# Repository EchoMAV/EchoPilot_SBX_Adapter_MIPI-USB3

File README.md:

Created using KiCad 7.0.10

This is an open-source payload/camera adapter designed for the EchoPilot SBX series of boards. It is meant for a 2 or 4-lane MIPI camera (22 pin 0.5mm spacing, standard Nvidia and Rpi pinout) and an optional FLIR boson in conjunction with OEM Camera VPC3 board (https://www.oemcameras.com/rhp-bos-vpc3-if.htm?search=vpc). The board also includes a 100Mbps Ethernet port using a JST GH connector.

6 Layer PCB, 4/4 mil spacing, min hole size is 0.2mm
Note impedance controlled traces for MIPI, USB and Ethernet. Trace width and spacing may need to be adjusted depending on the stackup and materials used in production.

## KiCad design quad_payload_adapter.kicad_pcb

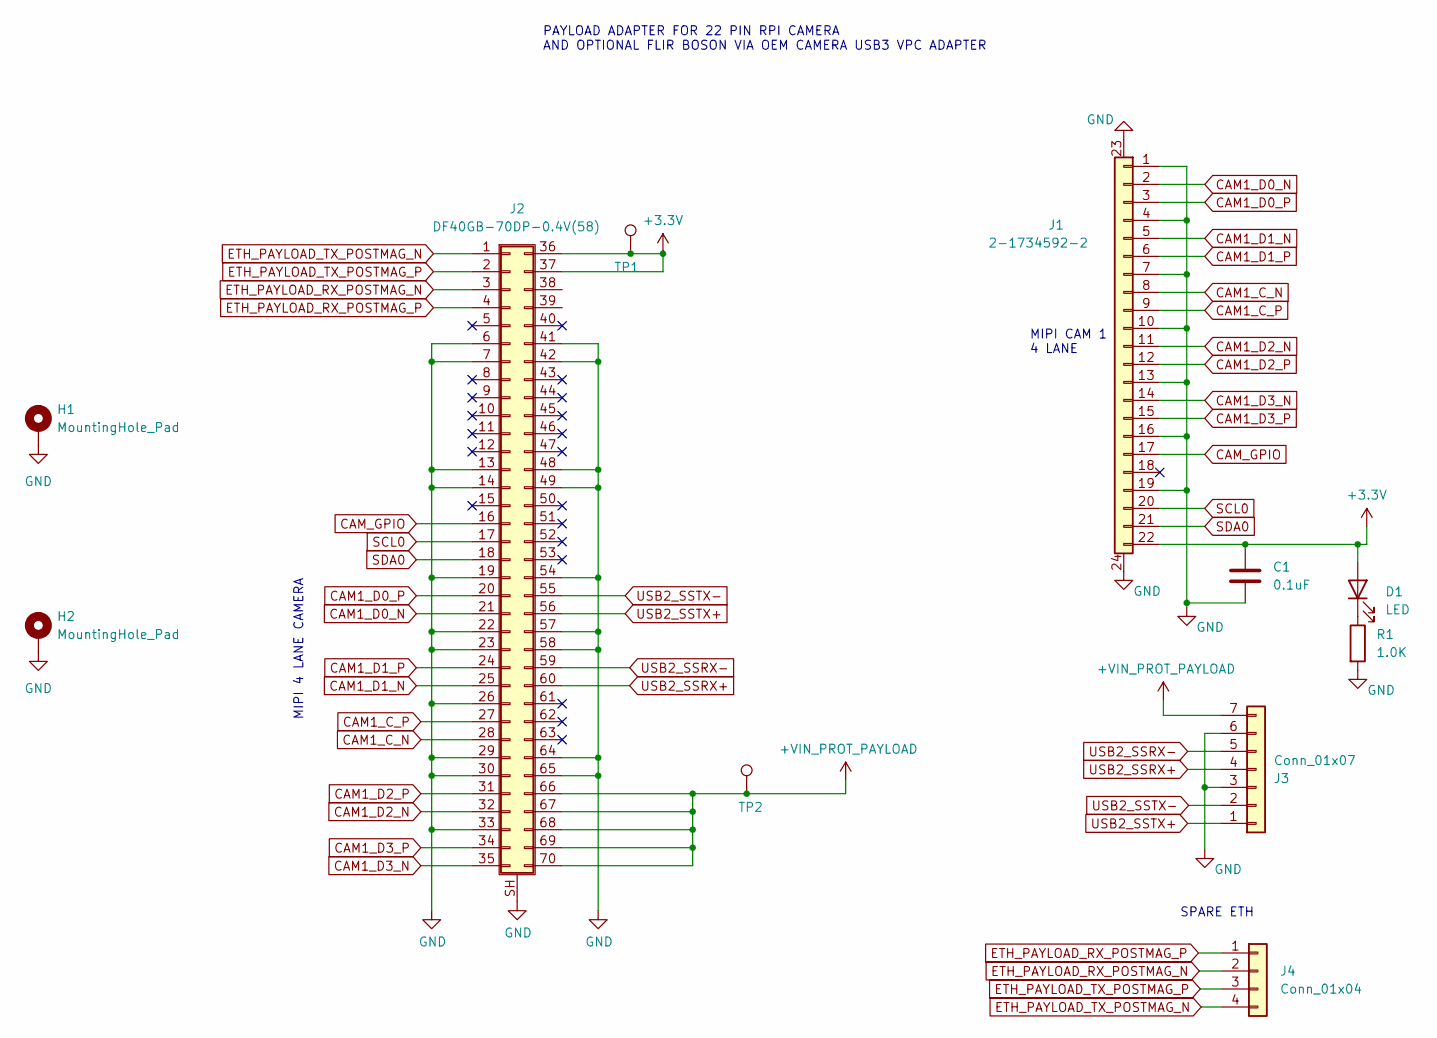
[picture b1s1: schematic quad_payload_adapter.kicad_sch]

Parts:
C1: 0.1uF; C_0201_0603Metric; Part Num GRM033R61E104KE14J
D1: LED; LED_0603_1608Metric; Part Num 150060VS75000
H1, H2: MountingHole_Pad; MountingHole_2.2mm_M2_Pad
J1: 2-1734592-2; CONN22_2-1734592-2; Part Num 2-1734592-2
J2: DF40GB-70DP-0.4V(58); DF40GB70DP04V58_REV1; Part Num DF40GB-70DP-0.4V(58)
J3: Conn_01x07; JST_SH_SM07B-SRSS-TB_1x07-1MP_P1.00mm_Horizontal; Part Num SM07B-SRSS-TB
J4: Conn_01x04; JST_GH_BM04B-GHS-TBT_1x04-1MP_P1.25mm_Vertical; Part Num BM04B-GHS-TBT
R1: 1.0K; R_0201_0603Metric; Part Num ERJ-1GEF1001C
TP1, TP2: TestPoint; TestPoint_Pad_D1.0mm; Part Num DNI

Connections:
+3.3V: C1.1, D1.2 (A), J1.22, J2.36, J2.37, TP1.1
+VIN_PROT_PAYLOAD: J2.66, J2.67, J2.68, J2.69, J2.70, J3.7, TP2.1
CAM1_C_N: J1.8, J2.28
CAM1_C_P: J1.9, J2.27
CAM1_D0_N: J1.2, J2.21
CAM1_D0_P: J1.3, J2.20
CAM1_D1_N: J1.5, J2.25
CAM1_D1_P: J1.6, J2.24
CAM1_D2_N: J1.11, J2.32
CAM1_D2_P: J1.12, J2.31
CAM1_D3_N: J1.14, J2.35
CAM1_D3_P: J1.15, J2.34
CAM_GPIO: J1.17, J2.16
ETH_PAYLOAD_RX_POSTMAG_N: J2.3, J4.2
ETH_PAYLOAD_RX_POSTMAG_P: J2.4, J4.1
ETH_PAYLOAD_TX_POSTMAG_N: J2.1, J4.4
ETH_PAYLOAD_TX_POSTMAG_P: J2.2, J4.3
GND: C1.2, H1.1, H2.1, J1.1, J1.4, J1.7, J1.10, J1.13, J1.16, J1.19, J1.23 (S1), J1.24 (S2), J2.6, J2.7, J2.13, J2.14, J2.19, J2.22, J2.23, J2.26, J2.29, J2.30, J2.33, J2.41, J2.42, J2.48, J2.49, J2.54, J2.57, J2.58, J2.64, J2.65, J2.SH (Shield), J3.3, J3.6, R1.2
unnamed: D1.1 (K), R1.1
SCL0: J1.20, J2.17
SDA0: J1.21, J2.18
USB2_SSRX+: J2.60, J3.4
USB2_SSRX-: J2.59, J3.5
USB2_SSTX+: J2.56, J3.1
USB2_SSTX-: J2.55, J3.2

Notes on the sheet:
PAYLOAD ADAPTER FOR 22 PIN RPI CAMERA AND OPTIONAL FLIR BOSON VIA OEM CAMERA USB3 VPC ADAPTER
MIPI CAM 1 4 LANE
MIPI 4 LANE CAMERA
SPARE ETH

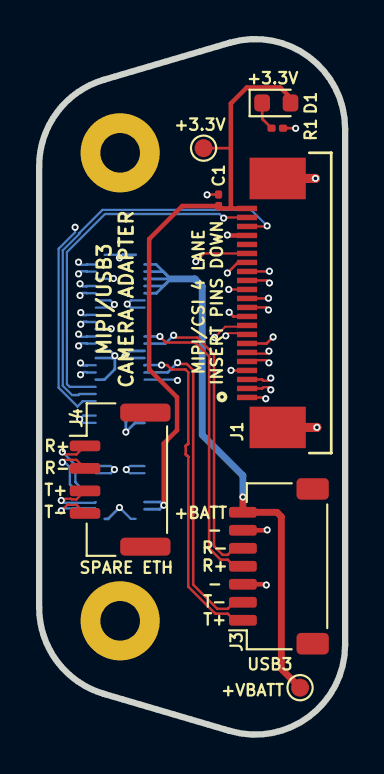
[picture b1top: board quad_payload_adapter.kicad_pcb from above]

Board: 6 copper layers, 17.0 x 38.6 mm, 11 parts (1 on the bottom side), 25 nets.

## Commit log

2024-02-01 first
